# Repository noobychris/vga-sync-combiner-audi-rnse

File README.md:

# VGA Sync Combiner for Audi RNS-E, 74HCT86 based

This project contains a small KiCad PCB for converting a VGA-style RGBHV signal into an RGBS signal suitable for the RGB video input of an Audi RNS-E navigation unit.

The board was designed for use with HDMI-to-VGA adapters or similar VGA/RGBHV sources. It passes the red, green and blue video signals through and combines the separate horizontal and vertical sync signals into one composite sync signal.

The circuit is based on the VGA to RGB+CSYNC adapter by Tomi Engdahl. The PCB is not a direct 1:1 copy of the original TTL output circuit. It adapts the basic 74HCT86 sync-combiner concept for this specific RNS-E use case, including a series resistor on the C-Sync output and practical connector/power options.

## Purpose

The Audi RNS-E RGB input expects RGBS video, while common VGA sources output RGBHV. This board converts the sync part from RGBHV to RGBS by combining H-Sync and V-Sync into one C-Sync signal. The RGB video lines are routed directly through the PCB.

## PCB

The PCB is designed to be hand-solder friendly. It uses larger SMD packages where practical, mainly 1206 passives and an SOIC-14 logic IC. The layout is intended for manual assembly rather than automated production.

The capacitors are MLCC parts, so they are non-polarized and can be soldered in either orientation. This avoids polarity mistakes during manual assembly.

Power for the logic IC can be selected by jumper:

| PCB label | Power source | Description | Notes |
|-----------|--------------|-------------|-------|
| `VGA` | VGA +5V | Via VGA Pin 9 | Requires an HDMI-to-VGA converter that supplies +5V on VGA Pin 9. Not all converters do this. Check the tested converter table before using this option. |
| `USB` | USB-C +5V | Via USB-C connector | Use this option if the converter does not provide +5V on VGA Pin 9. |
| `EXT` | External +5V | Via external JST input | Optional external 5V supply. Check the polarity marked on the PCB before applying power. |

> **Important:** Only one jumper position and one 5V power source must be used at a time. Do not connect multiple 5V sources simultaneously.

A converter may work correctly for video output while still not supplying +5V on VGA Pin 9. In that case, power the PCB through `USB` or `EXT`.

**Only one jumper position and one 5V power source must be used at a time. Do not connect multiple 5V sources simultaneously.**

The external JST input is intended as an optional 5V supply. Its polarity is marked directly on the PCB. Check polarity before applying power.

## Specifications

- Input: VGA RGBHV
- Output: RGBS (Composite Sync)
- Supply voltage: 5 V DC
- Typical current consumption: 15–20 mA
- Supported logic ICs:
  - 74HCT86 (recommended)
  - 74LS86 (supported)
- PCB dimensions: 31 × 31 mm
- PCB thickness: 1.6 mm

## ⚠️ Sync combiner operates without external power

In some setups, the sync combiner may appear to work even when no power supply is connected. This can happen due to backfeeding through the HSync and VSync input signals.

This is unintended behavior and should not be used as a valid power source. Always power the sync combiner from one of the supported 5V inputs.

## Tested (Micro) HDMI to VGA Converters with Raspberry Pi 4B &nbsp;&nbsp;&nbsp; 

**Recommended converter:**  

> The **Hama Video Adapter HDMI™ Plug to VGA Socket (00200344)** is the recommended option for this PCB. It has been tested successfully and provides +5 V on VGA pin 9, allowing the sync combiner to be powered directly through the VGA connection.
>
> Since the Hama adapter has a standard HDMI plug, a **Micro-HDMI-to-HDMI adapter, cable or compatible Raspberry Pi HDMI connector adapter** is additionally required.
>
> Since it has a female VGA output, a **VGA male-to-male gender changer** is also required.

| Converter | HDMI Input | VGA Output | HDMI Adapter | VGA Gender Changer | Price | Result | +5V on VGA Pin 9 | Recommendation | Link |
|-----------|------------|------------|--------------|--------------------|-------|--------|-----------------|----------------|------|
| 🏆 **Hama Video Adapter HDMI™ Plug to VGA Socket (00200344)** | HDMI | female | ✅ Required | ✅ Required | ~17 € | ✅ Working | ✅ Yes | ⭐ **Recommended** | [Hama](https://nordics.hama.com/00200344/hama-video-adapter-hdmi-plug-vga-socket-full-hd-1080p) |
| Official Raspberry Pi Micro-HDMI to VGA Cable | Micro HDMI | male | ❌ No | ❌ No | ~7 € | ✅ Working | ❌ No | Alternative with external PCB power | [The Pi Hut](https://thepihut.com/products/official-raspberry-pi-micro-hdmi-to-vga-cable) |
| Male Micro HDMI to Female VGA Adapter Active | Micro HDMI | female | ❌ No | ✅ Required | ~4 € | ✅ Working | ❌ No | Alternative with external PCB power | [AliExpress](https://aliexpress.com/item/1005006115048037.html) |
| BENFEI HDMI to VGA Adapter | HDMI | female | ✅ Required | ✅ Required | ~7 € | ✅ Working | ❌ No | Alternative with external PCB power | [Amazon](https://www.amazon.de/dp/B075GZ8DX7) |
| Twozoh Micro HDMI to VGA Adapter | Micro HDMI | male | ❌ No | ❌ No | ~14 € | ⚠️ Occasional picture interruptions | ✅ Yes | Not recommended | [Amazon](https://www.amazon.de/dp/B0CC9CVRDV) |
| Twozoh HDMI to VGA Adapter | HDMI | male | ✅ Required | ❌ No | ~14 € | ⚠️ Occasional picture interruptions | ✅ Yes | Not recommended | [Amazon](https://www.amazon.de/dp/B0BNTPLYZL) |
| Delock Adapter HDMI Micro-D male to VGA female (65470) | Micro HDMI | female | ❌ No | ✅ Required | ~16 € | ❌ Not working at all | ❌ No | Incompatible | [DeLock](https://www.delock.de/produkt/65470/merkmale.html?setLanguage=en) |

**HDMI Adapter:** A Micro-HDMI-to-HDMI adapter or cable is required for converters with a standard HDMI input when used with the Raspberry Pi 4B.

**VGA Gender Changer:** A VGA male-to-male gender changer is required for converters with a female VGA output.
## Optional EDID installer

This repository also includes an optional `install_edid.sh` script for the Audi RNS-E Raspberry Pi display setup.

The script can install/test EDID files or apply custom `800x480` HDMI timings. It is mainly intended for experimenting with the RNS-E RGB/RGBS video input and different HDMI/VGA or scaler setups.

I have included two `800x480` EDID files for the 193 / 2010 RNS-E:

```text
Karmannsport_RNSE_EDID.bin
pcbbc_Rpi_RNSE_800x480i_EDID.bin
```

## Audi RNS-E Connection

The board was made for an Audi RNS-E RGBS input setup. The RGB and C-Sync output can be wired to the corresponding RNS-E AV/RGB connector pins.
See the [Audi RNS-E pinout](docs/images/rns-e_pinout.jpg) for the connector reference.

## Case

A matching 3D-printable case is included. The case is intended to protect the PCB and make the adapter easier to install in a vehicle or cable harness.

The case files are located in:

```text
3d_print_case/
├─ vga_sync_combiner.3mf
├─ vga_sync_combiner.stl
└─ 3d_models/
   ├─ vga_sync_combiner_case.step
   └─ vga_sync_combiner_with_all_pcb_parts.step
```

## Repository structure

```text
/
├─ 3d_print_case/
│  ├─ 3d_models/
│  ├─ vga_sync_combiner.3mf
│  └─ vga_sync_combiner.stl
├─ bom/
│  ├─ bom_vga_sync_combiner_for_audi_rns-e_complete.csv
│  └─ bom_vga_sync_combiner_for_audi_rns-e_assembly_service.csv
├─ docs/
│  └─ images/
├─ edid_installer/
│  ├─ edid/
│  │  ├─ Karmannsport_RNSE_EDID.bin
│  │  └─ pcbbc_Rpi_RNSE_800x480i_EDID.bin
│  └─ install_edid.sh
├─ kicad_files/
│  ├─ 3dmodels/
│  ├─ gerber_to_order/
│  │  ├─ vga_sync_combiner_for_audi_rns-e_31.0x31.0mm_for_Default.zip
│  │  ├─ vga_sync_combiner_for_audi_rns-e_31.0x31.0mm_for_Elecrow.zip
│  │  ├─ vga_sync_combiner_for_audi_rns-e_31.0x31.0mm_for_FusionPCB.zip
│  │  ├─ vga_sync_combiner_for_audi_rns-e_31.0x31.0mm_for_JLCPCB.zip
│  │  └─ vga_sync_combiner_for_audi_rns-e_31.0x31.0mm_for_PCBWay.zip
│  ├─ vga_sync_combiner_for_rns-e_footprints.pretty/
│  ├─ vga_sync_combiner_for_rns-e_symbols.kicad_sym
│  ├─ vga_sync_combiner_for_audi_rns-e.kicad_pro
│  ├─ vga_sync_combiner_for_audi_rns-e.kicad_sch
│  ├─ vga_sync_combiner_for_audi_rns-e.kicad_pcb
│  └─ vga_sync_combiner_for_audi_rns-e.kicad_prl
└─ README.md
````

The BOM is located at:

```text
kicad_files/vga_sync_combiner_for_audi_rns-e.csv
```

The BOM also includes parts that are not mounted directly on the PCB, such as cables, crimp contacts, connector housings and jumper/shunt parts. It is therefore intended as a complete project BOM, not necessarily as a direct assembly BOM for PCB assembly services.

## Notes

This board is intended for experimental/custom RNS-E video input builds. It is not an official Audi product and has no relation to Audi.

The original Engdahl circuit is a TTL-level sync combiner. This PCB keeps the 74HCT86-based sync-combiner principle, but the output stage is adapted for this project. Depending on the target device, video source and wiring, the C-Sync output resistor may need adjustment.

## Credits

The sync-combining logic is based on the original [VGA to RGB + composite sync converter](https://www.epanorama.net/circuits/vga2rgbs.html) circuit by Tomi Engdahl, 1993–1996.

The included PCB adapts the concept for an Audi RNS-E RGBS input use case.

## License

The hardware design files in this repository, including schematics,
PCB layouts, Gerber files, manufacturing files, and documentation,
are licensed under the CERN Open Hardware Licence Version 2 –
Permissive (CERN-OHL-P-2.0).

See the [LICENSE](LICENSE) file for the full license text.

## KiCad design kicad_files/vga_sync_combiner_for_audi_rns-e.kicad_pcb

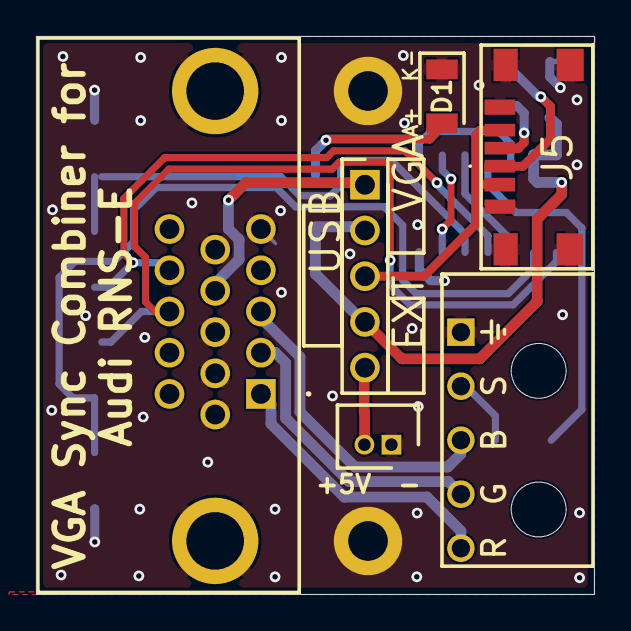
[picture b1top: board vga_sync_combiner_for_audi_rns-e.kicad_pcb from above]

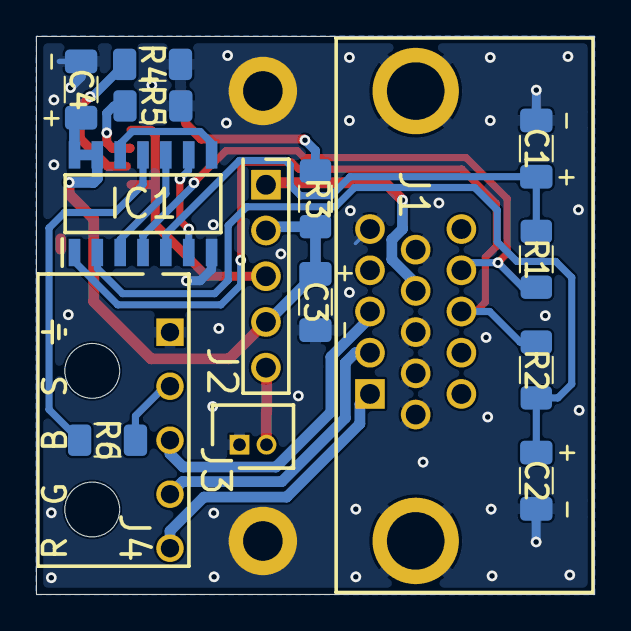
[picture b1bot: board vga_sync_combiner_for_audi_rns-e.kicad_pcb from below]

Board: 2 copper layers, 31.0 x 31.0 mm, 19 parts (11 on the bottom side), 20 nets.

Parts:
C1, C2, C3: 22uF; C_1206_3216Metric_Pad1.33x1.80mm_HandSolder
C4: 100nF; C_1206_3216Metric_Pad1.33x1.80mm_HandSolder
D1: PWR_LED; LEDC3216X120N
H1, H2: MountingHole_Pad; MountingHole_2.2mm_M2_DIN965_Pad
IC1: 74HCT86; SOIC127P600X175-14N
J1: VGA_RGBHV_IN; L77HDE15SD1CH4F
J2: POWER_SOURCE_JUMPER_HEADER; HDRV5W64P0X254_1X5_1270X254X854P
J3: JST ZR 1x2 Header; SHDR2W50P0X150_1X2_450X350X450P
J4: RGBS_OUT_PCB_HEADER; 214450985
J5: USB-C; USB4135GFA
R1, R2, R3: 2k2; R_1206_3216Metric_Pad1.30x1.75mm_HandSolder
R4, R5: 5k1; R_1206_3216Metric_Pad1.30x1.75mm_HandSolder
R6: 200R; R_1206_3216Metric_Pad1.30x1.75mm_HandSolder

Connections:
/+5V_JST: J2.5, J3.2
/+5V_LOAD: C3.1 (+), C4.1, IC1.13 (4B), IC1.14 (VCC), J2.2, J2.4, R3.1
/+5V_USB: J2.3, J5.A9, J5.B9
/+5V_VGA: J1.9, J2.1
/BLUE: J1.3, J4.3
/CC1: J5.A5, R4.1
/CC2: J5.B5, R5.1
/C_SYNC_OUT: J4.2, R6.2
/C_SYNC_PRE_R: IC1.11 (4Y), R6.1
/C_SYNC_RAW: IC1.8 (3Y), IC1.12 (4A)
/GREEN: J1.2, J4.4
/H_SYNC_DLY: C2.1 (+), IC1.2 (1B), R2.2
/H_SYNC_IN: IC1.1 (1A), J1.13, R2.1
/H_XOR_OUT: IC1.3 (1Y), IC1.10 (3B)
/LED_PWR: D1.2 (A), R3.2
/RED: J1.1, J4.5
/V_SYNC_DLY: C1.1 (+), IC1.5 (2B), R1.2
/V_SYNC_IN: IC1.4 (2A), J1.14, R1.1
/V_XOR_OUT: IC1.6 (2Y), IC1.9 (3A)
GND: C1.2 (-), C2.2 (-), C3.2 (-), C4.2, D1.1 (K), H1.1 (1_1), H2.1 (1_1), IC1.7 (GND), J1.5, J1.6, J1.7, J1.8, J1.10, J1.16 (MH1), J1.17 (MH2), J3.1, J4.1, J5.A12, J5.B12, J5.MP1, J5.MP2, J5.MP3, J5.MP4, R4.2, R5.2

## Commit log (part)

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2026-06-15 Rename vga_sync_combiner.3mf to vga_sync_combiner_case.3mf
2026-06-15 Rename vga_sync_combiner.stl to vga_sync_combiner_case.stl
2026-06-16 Rename vga_sync_combiner_case.3mf to vga_sync_combiner_for_rns-e_case.3mf
2026-06-16 Rename vga_sync_combiner_case.stl to vga_sync_combiner_for_rns-e_case.stl
2026-06-16 Rename vga_sync_combiner_case.step to vga_sync_combiner_for_rns-e_case.step
2026-06-16 Rename vga_sync_combiner_pcb.step to vga_sync_combiner_for_rns-e_pcb.step
2026-06-16 Rename vga_sync_combiner_pcb_and_case.step to vga_sync_combiner_for_rns-e_pcb_and_case.step
2026-06-16 Rename vga_sync_combiner_for_audi_rns-e.csv to bom_vga_sync_combiner_for_audi_rns-e_complete.csv
2026-06-16 Enhance README with image and additional details
    Added an image and improved the README content.
2026-06-19 Update options in converter_report.yml to use quotes
2026-06-19 Create converter_report.yml for compatibility reporting
    Add a template for Micro HDMI to VGA converter reports.
2026-06-29 README.md aktualisieren
